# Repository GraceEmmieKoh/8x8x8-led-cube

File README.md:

# 8x8x8-led-cube
Eagle project for 8x8x8 LED Cube (v5) PCB, using ESP32

This project was largely inspired by chr's LED Cube Instructables build here: https://www.instructables.com/Led-Cube-8x8x8/

I used an ESP32 as the main microcontroller. The LED's are controlled by switching on/off columns with 74HC595's, and by alternating between layers with PN2222's. The circuit requires a 12V power supply, which is stepped down to 5V using a LM2678-ADJ.
The cube is connected to the PCB through nine 8-pin JST connectors. Eight connectors are used to control each column (8 * 8 = 64), and one connector is used to control between each layer.

This project is currently unfinished. I plan to add a Fusion 360 CAD model to house the PCB, as well as code for the cube.

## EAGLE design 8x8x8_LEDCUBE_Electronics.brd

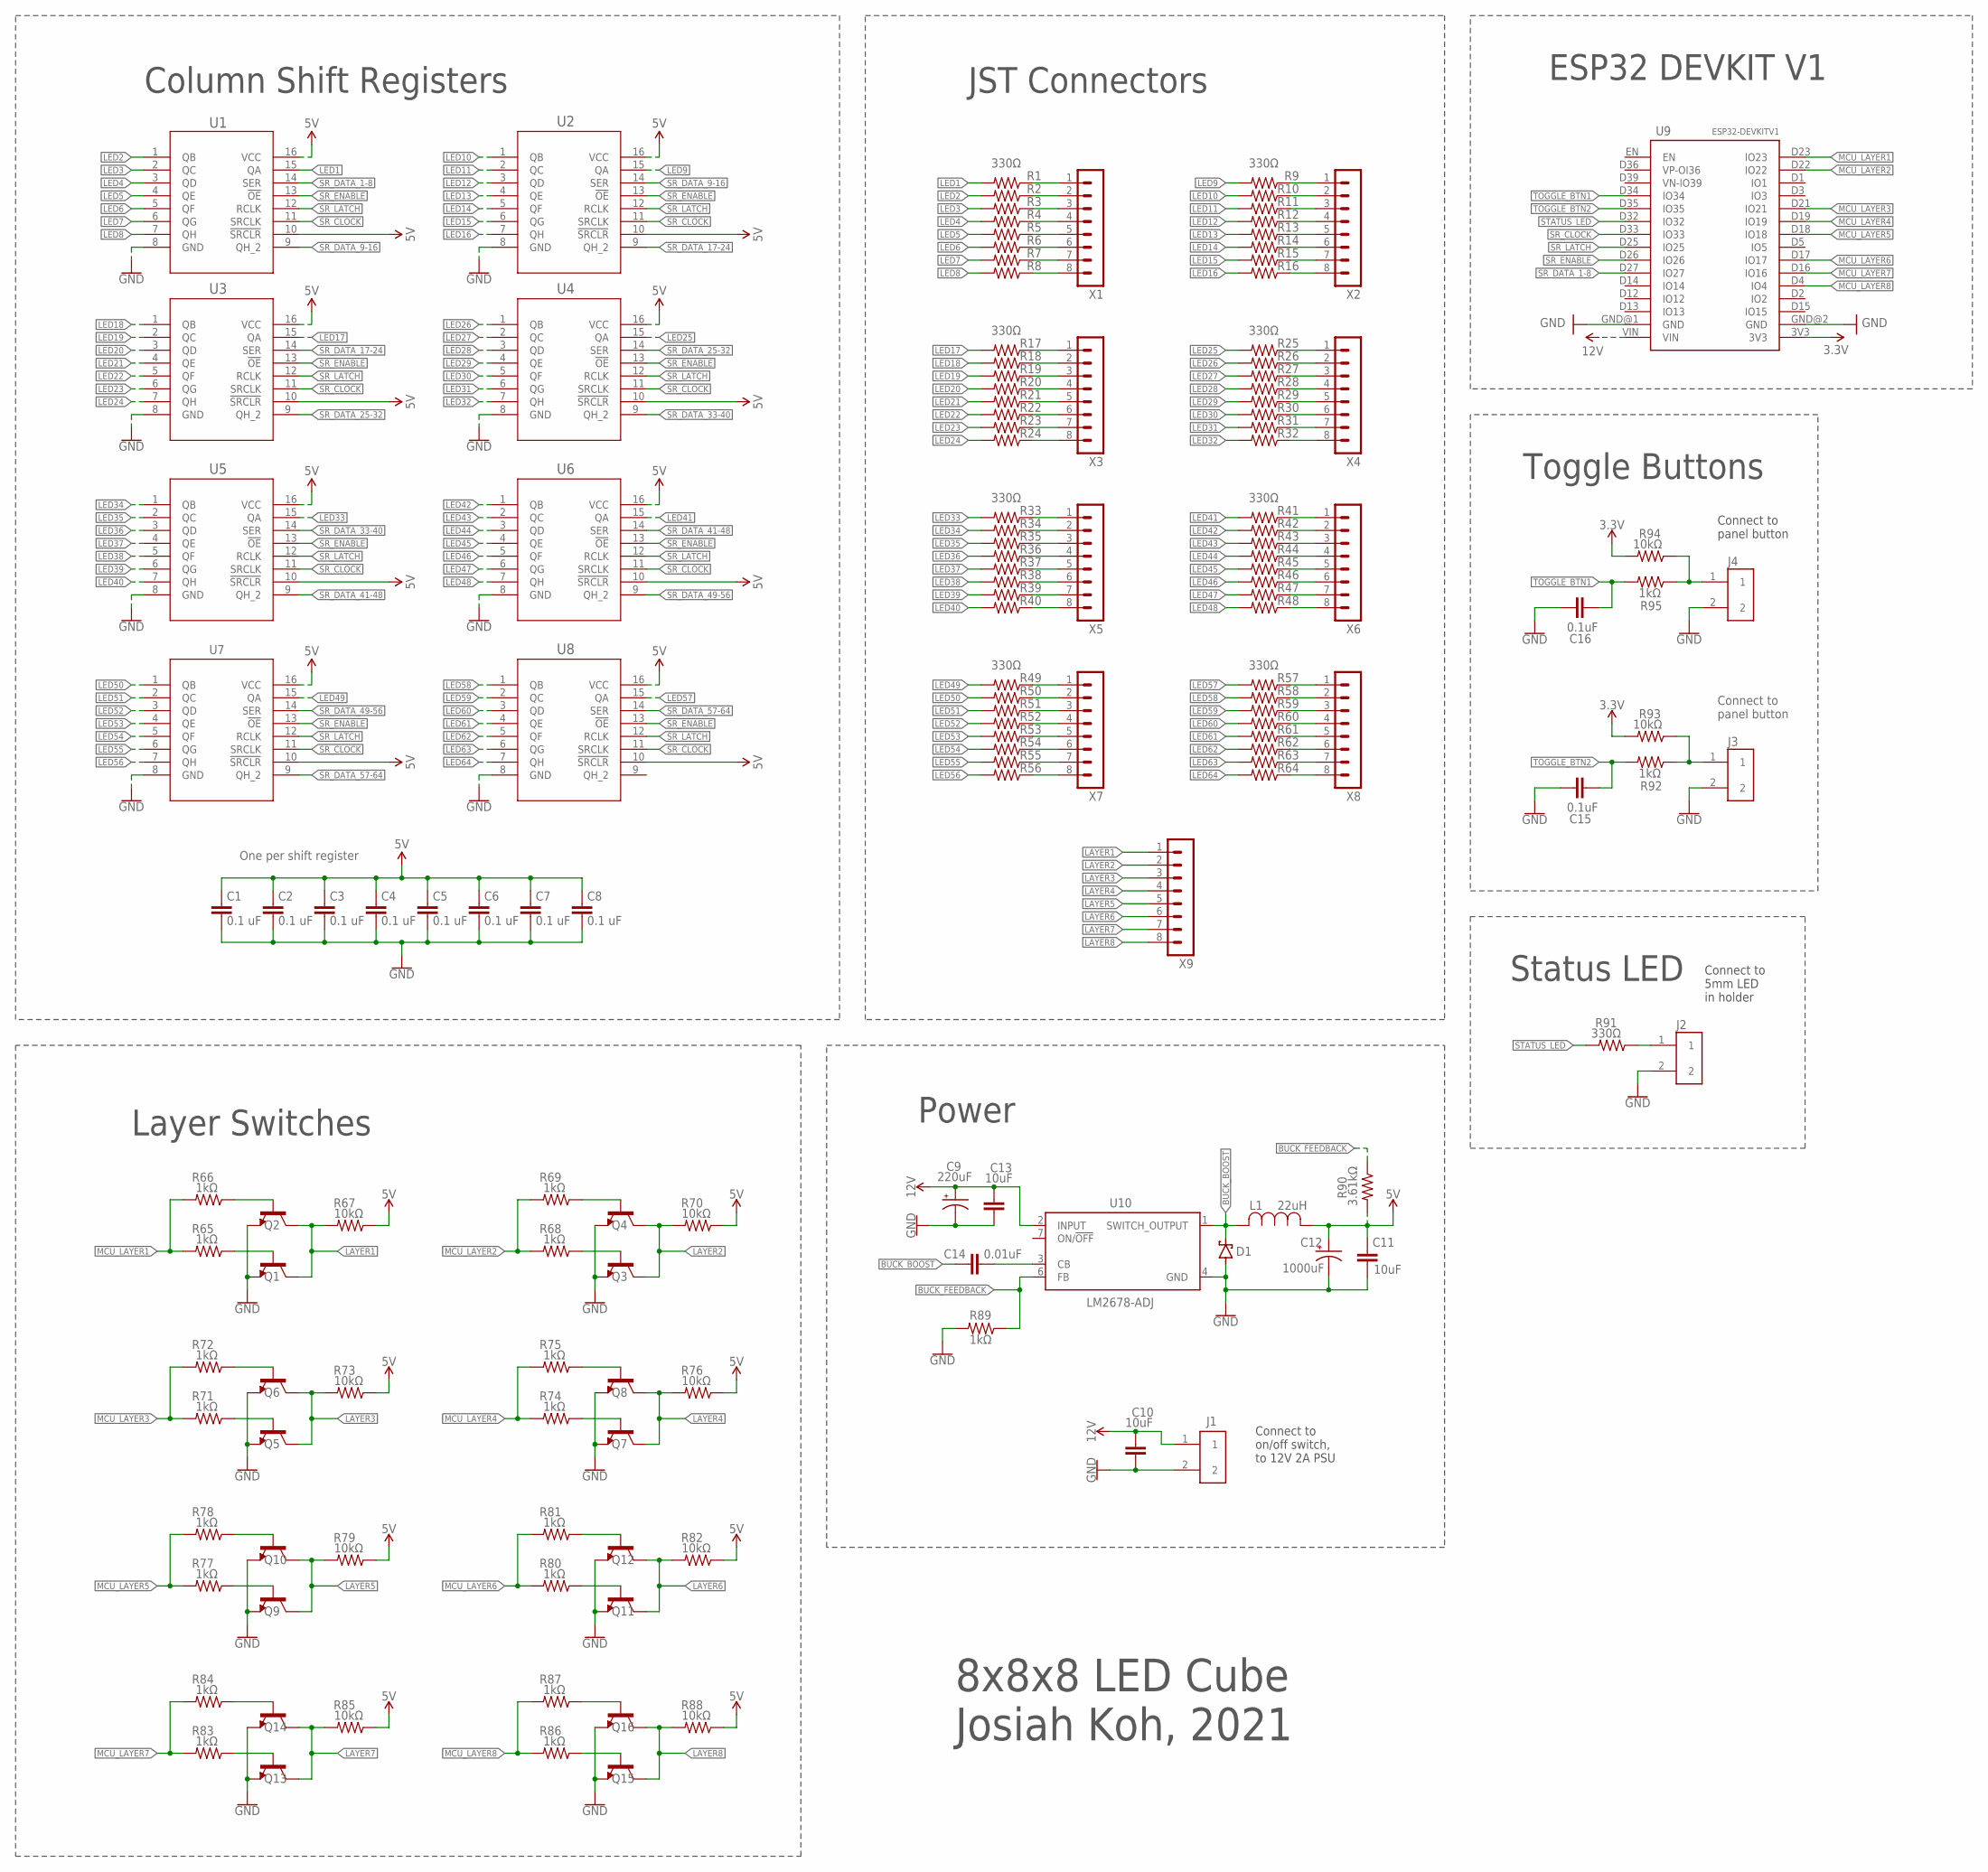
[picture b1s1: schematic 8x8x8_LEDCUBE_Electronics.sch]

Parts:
C1, C2, C3, C4, C5, C6, C7, C8: 0.1 uF; C0805
C9: 220uF; E3,5-10
C10, C11, C13: 10uF; C0805
C12: 1000uF; E3,5-10
C14: 0.01uF; C0805
C15, C16: 0.1uF; C0805
D1: STPS5L60S; SMC
J1, J2, J3, J4: 1935161; PHOENIX_1935161
L1: 22uH; AIAP-03_ABR
Q1, Q2, Q3, Q4, Q5, Q6, Q7, Q8, Q9, Q10, Q11, Q12, Q13, Q14, Q15, Q16: 600mA/40V; TO-92
R1, R2, R3, R4, R5, R6, R7, R8, R9, R10, R11, R12, R13, R14, R15, R16, R17, R18, R19, R20, R21, R22, R23, R24, R25, R26, R27, R28, R29, R30, R31, R32, R33, R34, R35, R36, R37, R38, R39, R40, R41, R42, R43, R44, R45, R46, R47, R48, R49, R50, R51, R52, R53, R54, R55, R56, R57, R58, R59, R60, R61, R62, R63, R64, R91: 330Ω; R0805
R65, R66, R68, R69, R71, R72, R74, R75, R77, R78, R80, R81, R83, R84, R86, R87, R89, R92, R95: 1kΩ; R0805
R67, R70, R73, R76, R79, R82, R85, R88, R93, R94: 10kΩ; R0805
R90: 3.61kΩ; R0805
U1, U2, U3, U4, U5, U6, U7, U8: SN74HC595N; N16
U9: ESP32DEVKITV1; ESP32-DEVKITV1
U10: LM2678-ADJ; TO127P1041X469X2199-7N
X1, X2, X3, X4, X5, X6, X7, X8, X9: B8B-PH-KL; B8B-PH-K-S

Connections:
3.3V: R93.2, R94.2, U9.3V3
5V: C1.1, C2.1, C3.1, C4.1, C5.1, C6.1, C7.1, C8.1, C11.1, C12.+, L1.1, R67.1, R70.1, R73.1, R76.1, R79.1, R82.1, R85.1, R88.1, R90.2, U1.10 (!SRCLR), U1.16 (VCC), U2.10 (!SRCLR), U2.16 (VCC), U3.10 (!SRCLR), U3.16 (VCC), U4.10 (!SRCLR), U4.16 (VCC), U5.10 (!SRCLR), U5.16 (VCC), U6.10 (!SRCLR), U6.16 (VCC), U7.10 (!SRCLR), U7.16 (VCC), U8.10 (!SRCLR), U8.16 (VCC)
12V: C9.+, C10.1, C13.1, J1.1, U9.VIN, U10.2 (INPUT)
BTN1_CONNECTOR: J4.1, R94.1, R95.1
BTN2_CONNECTOR: J3.1, R92.1, R93.1
BUCK_BOOST: C14.1, D1.C, L1.2, U10.1 (SWITCH_OUTPUT)
BUCK_FEEDBACK: R89.1, R90.1, U10.6 (FB)
GND: C1.2, C2.2, C3.2, C4.2, C5.2, C6.2, C7.2, C8.2, C9.-, C10.2, C11.2, C12.-, C13.2, C15.2, C16.2, D1.A, J1.2, J2.2, J3.2, J4.2, Q1.3 (E), Q2.3 (E), Q3.3 (E), Q4.3 (E), Q5.3 (E), Q6.3 (E), Q7.3 (E), Q8.3 (E), Q9.3 (E), Q10.3 (E), Q11.3 (E), Q12.3 (E), Q13.3 (E), Q14.3 (E), Q15.3 (E), Q16.3 (E), R89.2, U1.8 (GND), U2.8 (GND), U3.8 (GND), U4.8 (GND), U5.8 (GND), U6.8 (GND), U7.8 (GND), U8.8 (GND), U9.GND@1 (GND), U9.GND@2 (GND), U10.4 (GND)
LAYER1: Q1.1 (C), Q2.1 (C), R67.2, X9.1
LAYER2: Q3.1 (C), Q4.1 (C), R70.2, X9.2
LAYER3: Q5.1 (C), Q6.1 (C), R73.2, X9.3
LAYER4: Q7.1 (C), Q8.1 (C), R76.2, X9.4
LAYER5: Q9.1 (C), Q10.1 (C), R79.2, X9.5
LAYER6: Q11.1 (C), Q12.1 (C), R82.2, X9.6
LAYER7: Q13.1 (C), Q14.1 (C), R85.2, X9.7
LAYER8: Q15.1 (C), Q16.1 (C), R88.2, X9.8
LED1: R1.2, U1.15 (QA)
LED2: R2.2, U1.1 (QB)
LED3: R3.2, U1.2 (QC)
LED4: R4.2, U1.3 (QD)
LED5: R5.2, U1.4 (QE)
LED6: R6.2, U1.5 (QF)
LED7: R7.2, U1.6 (QG)
LED8: R8.2, U1.7 (QH)
LED9: R9.2, U2.15 (QA)
LED10: R10.2, U2.1 (QB)
LED11: R11.2, U2.2 (QC)
LED12: R12.2, U2.3 (QD)
LED13: R13.2, U2.4 (QE)
LED14: R14.2, U2.5 (QF)
LED15: R15.2, U2.6 (QG)
LED16: R16.2, U2.7 (QH)
LED17: R17.2, U3.15 (QA)
LED18: R18.2, U3.1 (QB)
LED19: R19.2, U3.2 (QC)
LED20: R20.2, U3.3 (QD)
LED21: R21.2, U3.4 (QE)
LED22: R22.2, U3.5 (QF)
LED23: R23.2, U3.6 (QG)
LED24: R24.2, U3.7 (QH)
LED25: R25.2, U4.15 (QA)
LED26: R26.2, U4.1 (QB)
LED27: R27.2, U4.2 (QC)
LED28: R28.2, U4.3 (QD)
LED29: R29.2, U4.4 (QE)
LED30: R30.2, U4.5 (QF)
LED31: R31.2, U4.6 (QG)
LED32: R32.2, U4.7 (QH)
LED33: R33.2, U5.15 (QA)
LED34: R34.2, U5.1 (QB)
LED35: R35.2, U5.2 (QC)
LED36: R36.2, U5.3 (QD)
LED37: R37.2, U5.4 (QE)
LED38: R38.2, U5.5 (QF)
LED39: R39.2, U5.6 (QG)
LED40: R40.2, U5.7 (QH)
LED41: R41.2, U6.15 (QA)
LED42: R42.2, U6.1 (QB)
LED43: R43.2, U6.2 (QC)
LED44: R44.2, U6.3 (QD)
LED45: R45.2, U6.4 (QE)
LED46: R46.2, U6.5 (QF)
LED47: R47.2, U6.6 (QG)
LED48: R48.2, U6.7 (QH)
LED49: R49.2, U7.15 (QA)
LED50: R50.2, U7.1 (QB)
LED51: R51.2, U7.2 (QC)
LED52: R52.2, U7.3 (QD)
LED53: R53.2, U7.4 (QE)
LED54: R54.2, U7.5 (QF)
LED55: R55.2, U7.6 (QG)
LED56: R56.2, U7.7 (QH)
LED57: R57.2, U8.15 (QA)
LED58: R58.2, U8.1 (QB)
LED59: R59.2, U8.2 (QC)
LED60: R60.2, U8.3 (QD)
LED61: R61.2, U8.4 (QE)
LED62: R62.2, U8.5 (QF)
LED63: R63.2, U8.6 (QG)
LED64: R64.2, U8.7 (QH)
MCU_LAYER1: R65.2, R66.2, U9.D23 (IO23)
MCU_LAYER2: R68.2, R69.2, U9.D22 (IO22)
MCU_LAYER3: R71.2, R72.2, U9.D21 (IO21)
MCU_LAYER4: R74.2, R75.2, U9.D19 (IO19)
MCU_LAYER5: R77.2, R78.2, U9.D18 (IO18)
MCU_LAYER6: R80.2, R81.2, U9.D17 (IO17)
MCU_LAYER7: R83.2, R84.2, U9.D16 (IO16)
MCU_LAYER8: R86.2, R87.2, U9.D4 (IO4)
unnamed: Q1.2 (B), R65.1
unnamed: Q2.2 (B), R66.1
unnamed: Q3.2 (B), R68.1
unnamed: Q4.2 (B), R69.1
unnamed: Q5.2 (B), R71.1
unnamed: Q6.2 (B), R72.1
unnamed: Q7.2 (B), R74.1
unnamed: Q8.2 (B), R75.1
unnamed: Q9.2 (B), R77.1
unnamed: Q10.2 (B), R78.1
unnamed: Q11.2 (B), R80.1
unnamed: Q12.2 (B), R81.1
unnamed: Q13.2 (B), R83.1
unnamed: Q14.2 (B), R84.1
unnamed: Q15.2 (B), R86.1
unnamed: Q16.2 (B), R87.1
unnamed: J2.1, R91.1
unnamed: R1.1, X1.1
unnamed: C14.2, U10.3 (CB)
unnamed: R2.1, X1.2
unnamed: R3.1, X1.3
unnamed: R4.1, X1.4
unnamed: R5.1, X1.5
unnamed: R6.1, X1.6
unnamed: R7.1, X1.7
unnamed: R8.1, X1.8
unnamed: R9.1, X2.1
unnamed: R10.1, X2.2
unnamed: R11.1, X2.3
unnamed: R12.1, X2.4
unnamed: R13.1, X2.5
unnamed: R14.1, X2.6
unnamed: R15.1, X2.7
unnamed: R16.1, X2.8
unnamed: R17.1, X3.1
unnamed: R18.1, X3.2
unnamed: R19.1, X3.3
unnamed: R20.1, X3.4
unnamed: R21.1, X3.5
unnamed: R22.1, X3.6
unnamed: R23.1, X3.7
unnamed: R24.1, X3.8
unnamed: R25.1, X4.1
unnamed: R26.1, X4.2
unnamed: R27.1, X4.3
unnamed: R28.1, X4.4
unnamed: R29.1, X4.5
unnamed: R30.1, X4.6
unnamed: R31.1, X4.7
unnamed: R32.1, X4.8
unnamed: R33.1, X5.1
unnamed: R34.1, X5.2
unnamed: R35.1, X5.3
unnamed: R36.1, X5.4
unnamed: R37.1, X5.5
unnamed: R38.1, X5.6
unnamed: R39.1, X5.7
unnamed: R40.1, X5.8
unnamed: R41.1, X6.1
unnamed: R42.1, X6.2
unnamed: R43.1, X6.3
unnamed: R44.1, X6.4
unnamed: R45.1, X6.5
unnamed: R46.1, X6.6
unnamed: R47.1, X6.7
unnamed: R48.1, X6.8
unnamed: R49.1, X7.1
unnamed: R50.1, X7.2
unnamed: R51.1, X7.3
unnamed: R52.1, X7.4
unnamed: R53.1, X7.5
unnamed: R54.1, X7.6
unnamed: R55.1, X7.7
unnamed: R56.1, X7.8
unnamed: R57.1, X8.1
unnamed: R58.1, X8.2
unnamed: R59.1, X8.3
unnamed: R60.1, X8.4
unnamed: R61.1, X8.5
unnamed: R62.1, X8.6
unnamed: R63.1, X8.7
unnamed: R64.1, X8.8
SR_CLOCK: U1.11 (SRCLK), U2.11 (SRCLK), U3.11 (SRCLK), U4.11 (SRCLK), U5.11 (SRCLK), U6.11 (SRCLK), U7.11 (SRCLK), U8.11 (SRCLK), U9.D33 (IO33)
SR_DATA_1-8: U1.14 (SER), U9.D27 (IO27)
SR_DATA_9-16: U1.9 (QH_2), U2.14 (SER)
SR_DATA_17-24: U2.9 (QH_2), U3.14 (SER)
SR_DATA_25-32: U3.9 (QH_2), U4.14 (SER)
SR_DATA_33-40: U4.9 (QH_2), U5.14 (SER)
SR_DATA_41-48: U5.9 (QH_2), U6.14 (SER)
SR_DATA_49-56: U6.9 (QH_2), U7.14 (SER)
SR_DATA_57-64: U7.9 (QH_2), U8.14 (SER)
SR_ENABLE: U1.13 (!OE), U2.13 (!OE), U3.13 (!OE), U4.13 (!OE), U5.13 (!OE), U6.13 (!OE), U7.13 (!OE), U8.13 (!OE), U9.D26 (IO26)
SR_LATCH: U1.12 (RCLK), U2.12 (RCLK), U3.12 (RCLK), U4.12 (RCLK), U5.12 (RCLK), U6.12 (RCLK), U7.12 (RCLK), U8.12 (RCLK), U9.D25 (IO25)
STATUS_LED: R91.2, U9.D32 (IO32)
TOGGLE_BTN1: C16.1, R95.2, U9.D34 (IO34)
TOGGLE_BTN2: C15.1, R92.2, U9.D35 (IO35)

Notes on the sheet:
Toggle Buttons
Column Shift Registers
Connect to panel button
One per shift register
Layer Switches
ESP32 DEVKIT V1
Connect to on/off switch, to 12V 2A PSU
Power
Connect to 5mm LED in holder
Status LED
JST Connectors
8x8x8 LED Cube Josiah Koh, 2021

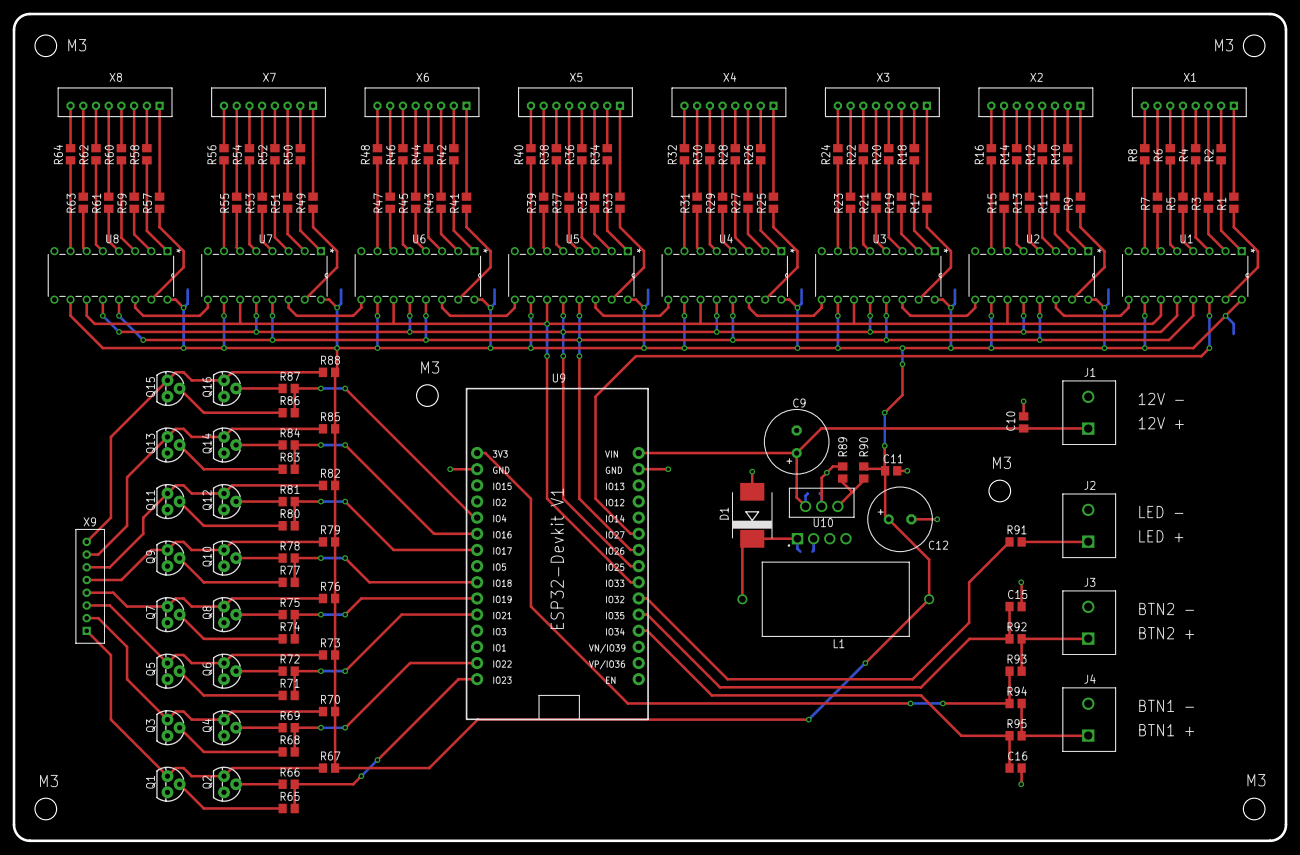
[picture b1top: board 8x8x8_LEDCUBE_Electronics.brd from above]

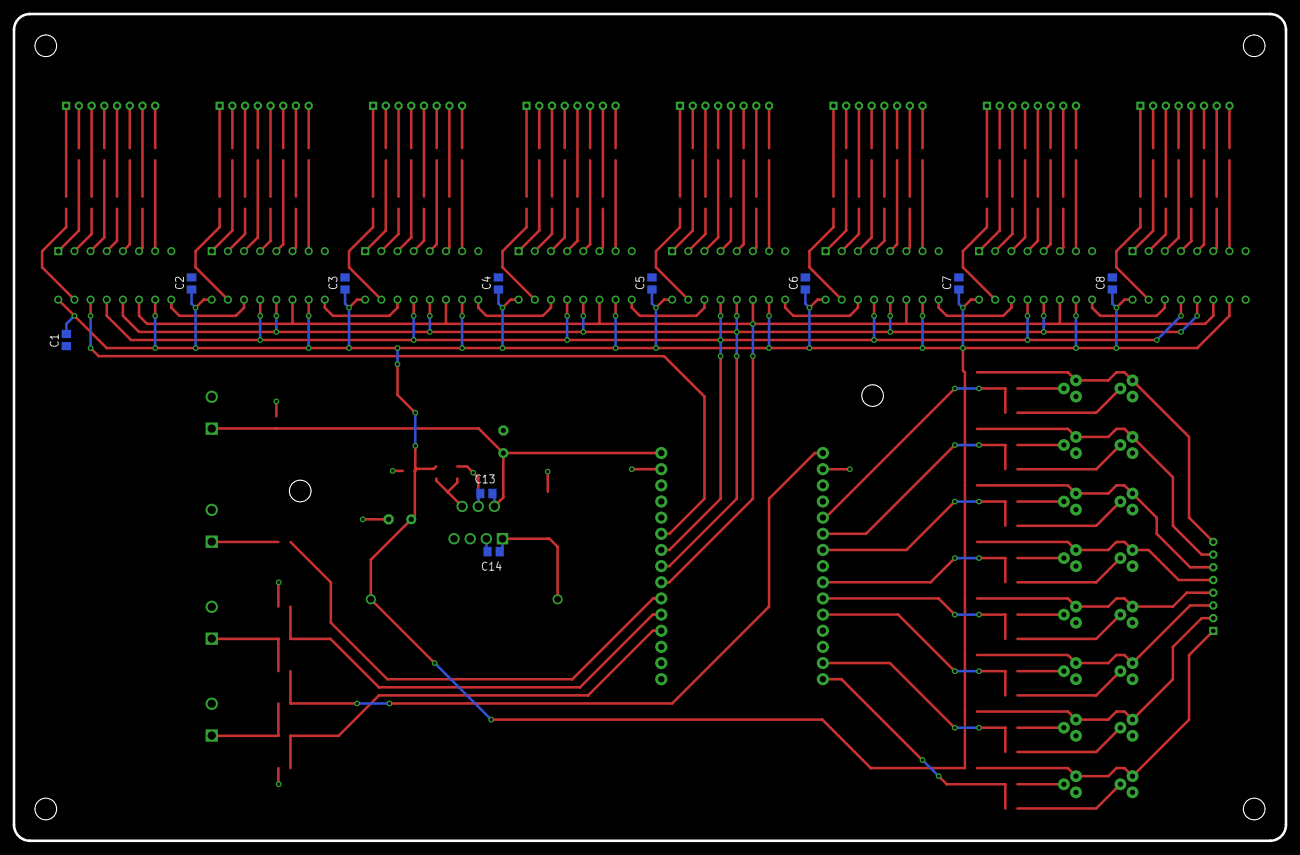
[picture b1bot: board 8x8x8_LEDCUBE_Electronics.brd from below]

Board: 2 copper layers, 200.0 x 130.0 mm, 152 parts (10 on the bottom side), 184 nets.

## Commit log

2021-01-13 Added files to repo
2021-01-13 Wrote README
2021-01-19 Added BOM
    I already own the iems with no DigiKey number

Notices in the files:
parts and their libraries:
SparkFun-DiscreteSemi: Licensing: Creative Commons ShareAlike 4.0 International - https://creativecommons.org/licenses/by-sa/4.0
